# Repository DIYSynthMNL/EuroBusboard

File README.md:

# EuroBusboard

A Eurorack bus board with **8 module slots**, distributing **±12V + GND** across multiple connector formats. The project has three PCB variants in the same KiCad project: **10-pin IDC + JST combined**, **10-pin IDC only**, and **JST only**.

> For the Doepfer-standard 16-pin IDC variant (with `+5V`, `CV`, `Gate` rails additionally distributed), see the sibling repo: **[EuroBusboard-8-IDC-16PIN](https://github.com/DIYSynthMNL/EuroBusboard-8-IDC-16PIN)**.

## Variants

The KiCad project contains four configurations. Pick one when fabricating the PCB:

| Variant | KiCad file | Per-slot connectors | Use case |
|---|---|---|---|
| **16-pin IDC** (Doepfer A-100) | (in separate repo: [EuroBusboard-8-IDC-16PIN](https://github.com/DIYSynthMNL/EuroBusboard-8-IDC-16PIN)) | 1× 16-pin IDC | Modules with full Doepfer ribbon cables (±12V + GND + +5V + CV + Gate) |
| **10-pin IDC + JST (combined)** | `eurobusboard_idc_jst_8.kicad_pcb` | 1× 10-pin IDC + 1× 3-pin JST | Maximum flexibility — accepts both connector types per slot |
| **10-pin IDC only** | `eurobusboard_idc_8.kicad_pcb` | 1× 10-pin IDC | Compact, IDC-only modules |
| **JST only** | `eurobusboard_jst_8.kicad_pcb` | 1× 3-pin JST | DIY modules that use only the 3-pin JST power input |

All variants share the same power-input + reverse-protection + filter section. Only the per-slot connectors differ.

## Pinout (10-pin IDC, Eurorack subset of Doepfer A-100)

Looking at the IDC connector with the keyway (red stripe) on the *bottom*:

```
Pin   10  9   8   7   6   5   4   3   2   1
      +12 +12 GND GND GND GND GND GND -12 -12
```

`-12V` is on pin 1 / 2 (the red-stripe side) — Eurorack convention. `+12V` is on pin 9 / 10 (opposite side). Six GND pins in the middle provide low-impedance ground return.

The **3-pin JST** is:

| JST pin | Net |
|---|---|
| 1 | +12V |
| 2 | GND |
| 3 | -12V |

## Schematic

- Latest: **Rev 0.1** ([EuroBusboard-Schematic-rev0.1.pdf](Schematic%20PDFs/EuroBusboard-Schematic-rev0.1.pdf)) — 3 sheets, one per non-16-pin variant

## Power input / protection

Same circuit on all three sheets, just renamed nets per variant:

```
External ±12V supply
   │
   ├──[D3 / D14 / D9   1N4007 reverse-polarity diode on +12V]──┬── +12V bus
   │                                                            │
   │                                                            [C1 / C7 / C5   100µF bulk cap]
   │                                                            │
   │                                                            [D1 / D13 / D11  +12V indicator LED + R1/R7/R5 10K]
   │
   └──[D4 / D16 / D10  1N4007 reverse-polarity diode on -12V]──┬── -12V bus
                                                                │
                                                                [C2 / C8 / C6   100µF bulk cap]
                                                                │
                                                                [D2 / D15 / D12  -12V indicator LED + R2/R8/R6 10K]
```

Additional features (combined-variant only):
- **Power Thru** (J20, J21) — daisy-chain to another bus board
- **Test points** TP1 (+12V), TP2 (GND), TP3 (-12V) for DMM probing

## Design notes

**1N4007 diodes have a real voltage drop.** At a peak transient current of 1 A across each rail (with all 8 modules pulling momentarily), the diode drops about **1.0 V** — modules see only ~11 V on the rail instead of 12 V. For most analog modules this is harmless; for tight regulators (e.g. an LM7805 regulating to +5V from +12V supply that's actually 11V), it can reduce headroom. **A 1N5817 Schottky (~0.4 V drop)** would be a near-drop-in upgrade. See [issue](../../issues).

**No +5V or CV/Gate rails.** The 10-pin IDC variants don't distribute +5V (which most digital modules need) or CV/Gate (which the Doepfer A-100 standard provides for keyboard-bus signals). Modules requiring +5V must generate their own (via a 78M05 + the +12V rail — which is what most DIYSynthMNL modules do). For full Doepfer compatibility, use the 16-pin IDC variant in [EuroBusboard-8-IDC-16PIN](https://github.com/DIYSynthMNL/EuroBusboard-8-IDC-16PIN).

**Bulk capacitance.** 100 µF at the input is reasonable for a small case. For a fully-loaded board with current-hungry modules (digital sequencers, OLEDs, several VCAs), consider adding ~10 µF ceramics near each IDC connector for transient suppression.

## License

[GPLv3](LICENSE) — strong copyleft. **Note:** this is different from most DIYSynthMNL modules (which use CC-BY-NC-SA 4.0 for hardware, MIT for firmware). Confirm this license is intentional — for a passive bus board, MIT or CC-BY-SA may be more appropriate. See [issue](../../issues).

## Build status

What's ready for builders today, and what's still on the TODO list:

- [x] Schematic — Rev 0.1 ([EuroBusboard-Schematic-rev0.1.pdf](Schematic%20PDFs/EuroBusboard-Schematic-rev0.1.pdf))
- [ ] PCB layout — in progress — four variants in `kicad/`, no rev marker yet
- [ ] Gerber files for fabrication — none yet
- [ ] BOM — bus boards are simple; the schematic doubles as the BOM (LED color, diode replacement to Schottky if you take the recommendation above, etc.)
- [x] Photos of an assembled board — see [photos/](photos/)
- [x] License — [LICENSE](LICENSE) (GPLv3 — see note above)

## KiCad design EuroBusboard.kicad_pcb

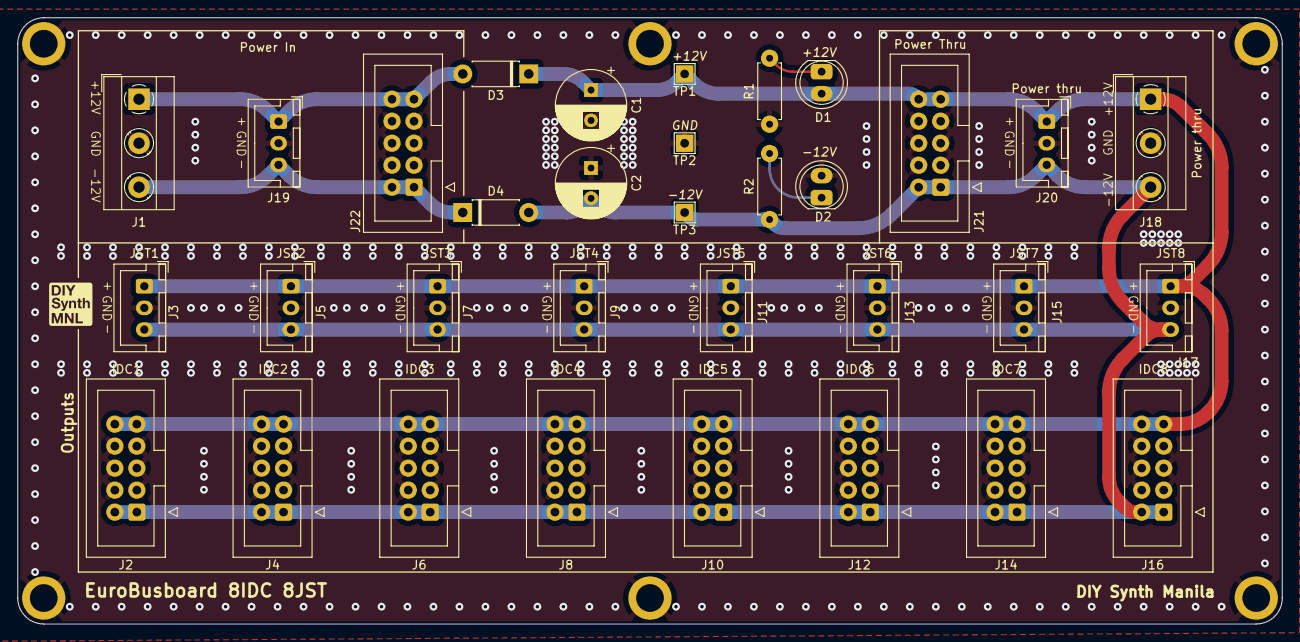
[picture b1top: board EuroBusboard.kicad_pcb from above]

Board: 2 copper layers, 146.0 x 70.0 mm, 39 parts (0 on the bottom side), 7 nets.

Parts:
C1, C2: 100uF; CP_Radial_D8.0mm_P3.50mm
D1: +12V; LED_D5.0mm_BigPads
D2: -12V; LED_D5.0mm_BigPads
D3, D4: 4007; D_DO-41_SOD81_P7.62mm_Horizontal_BigPads
H1, H2, H3, H4, H5, H6: MountingHole_Pad; MountingHole_M3_Standoff_Pad
J1: Power In; TerminalBlock_MetzConnect_Type101_RT01603HBWC_1x03_P5.08mm_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
J2: IDC1; IDC-Header_2x05_P2.54mm_Vertical_BigPads
J3: JST1; Eurorack_power_jst_3P
J4: IDC2; IDC-Header_2x05_P2.54mm_Vertical_BigPads
J5: JST2; Eurorack_power_jst_3P
J6: IDC3; IDC-Header_2x05_P2.54mm_Vertical_BigPads
J7: JST3; Eurorack_power_jst_3P
J8: IDC4; IDC-Header_2x05_P2.54mm_Vertical_BigPads
J9: JST4; Eurorack_power_jst_3P
J10: IDC5; IDC-Header_2x05_P2.54mm_Vertical_BigPads
J11: JST5; Eurorack_power_jst_3P
J12: IDC6; IDC-Header_2x05_P2.54mm_Vertical_BigPads
J13: JST6; Eurorack_power_jst_3P
J14: IDC7; IDC-Header_2x05_P2.54mm_Vertical_BigPads
J15: JST7; Eurorack_power_jst_3P
J16: IDC8; IDC-Header_2x05_P2.54mm_Vertical_BigPads
J17: JST8; Eurorack_power_jst_3P
J18: Power thru; TerminalBlock_MetzConnect_Type101_RT01603HBWC_1x03_P5.08mm_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
J19: Power In; Eurorack_power_jst_3P
J20: Power thru; Eurorack_power_jst_3P
J21: Power Thru; IDC-Header_2x05_P2.54mm_Vertical_BigPads
J22: Power In; IDC-Header_2x05_P2.54mm_Vertical_BigPads
R1, R2: 10K; R_quarter_watt_L6.3mm_D2.5mm_P7.62mm
TP1: +12V; TestPoint_THTPad_2.0x2.0mm_Drill1.0mm
TP2: GND; TestPoint_THTPad_2.0x2.0mm_Drill1.0mm
TP3: -12V; TestPoint_THTPad_2.0x2.0mm_Drill1.0mm

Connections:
/+12V: C1.1, D1.2 (A), D3.1 (K), J2.9 (+12V), J2.10 (+12V), J3.1 (+12v), J4.9 (+12V), J4.10 (+12V), J5.1 (+12v), J6.9 (+12V), J6.10 (+12V), J7.1 (+12v), J8.9 (+12V), J8.10 (+12V), J9.1 (+12v), J10.9 (+12V), J10.10 (+12V), J11.1 (+12v), J12.9 (+12V), J12.10 (+12V), J13.1 (+12v), J14.9 (+12V), J14.10 (+12V), J15.1 (+12v), J16.9 (+12V), J16.10 (+12V), J17.1 (+12v), J18.1, J20.1 (+12v), J21.9 (+12V), J21.10 (+12V), TP1.1
/+12V_IN: D3.2 (A), J1.1, J19.1 (+12v), J22.9 (+12V), J22.10 (+12V)
/-12V: C2.2, D4.2 (A), J2.1 (-12V), J2.2 (-12V), J3.3 (-12v), J4.1 (-12V), J4.2 (-12V), J5.3 (-12v), J6.1 (-12V), J6.2 (-12V), J7.3 (-12v), J8.1 (-12V), J8.2 (-12V), J9.3 (-12v), J10.1 (-12V), J10.2 (-12V), J11.3 (-12v), J12.1 (-12V), J12.2 (-12V), J13.3 (-12v), J14.1 (-12V), J14.2 (-12V), J15.3 (-12v), J16.1 (-12V), J16.2 (-12V), J17.3 (-12v), J18.3, J20.3 (-12v), J21.1 (-12V), J21.2 (-12V), R2.1, TP3.1
/-12V_IN: D4.1 (K), J1.3, J19.3 (-12v), J22.1 (-12V), J22.2 (-12V)
/GND: C1.2, C2.1, D2.2 (A), H1.1, H2.1, H3.1, H4.1, H5.1, H6.1, J1.2, J2.3 (GND), J2.4 (GND), J2.5 (GND), J2.6 (GND), J2.7 (GND), J2.8 (GND), J3.2 (GND), J4.3 (GND), J4.4 (GND), J4.5 (GND), J4.6 (GND), J4.7 (GND), J4.8 (GND), J5.2 (GND), J6.3 (GND), J6.4 (GND), J6.5 (GND), J6.6 (GND), J6.7 (GND), J6.8 (GND), J7.2 (GND), J8.3 (GND), J8.4 (GND), J8.5 (GND), J8.6 (GND), J8.7 (GND), J8.8 (GND), J9.2 (GND), J10.3 (GND), J10.4 (GND), J10.5 (GND), J10.6 (GND), J10.7 (GND), J10.8 (GND), J11.2 (GND), J12.3 (GND), J12.4 (GND), J12.5 (GND), J12.6 (GND), J12.7 (GND), J12.8 (GND), J13.2 (GND), J14.3 (GND), J14.4 (GND), J14.5 (GND), J14.6 (GND), J14.7 (GND), J14.8 (GND), J15.2 (GND), J16.3 (GND), J16.4 (GND), J16.5 (GND), J16.6 (GND), J16.7 (GND), J16.8 (GND), J17.2 (GND), J18.2, J19.2 (GND), J20.2 (GND), J21.3 (GND), J21.4 (GND), J21.5 (GND), J21.6 (GND), J21.7 (GND), J21.8 (GND), J22.3 (GND), J22.4 (GND), J22.5 (GND), J22.6 (GND), J22.7 (GND), J22.8 (GND), R1.1, TP2.1
unnamed: D1.1 (K), R1.2
unnamed: D2.1 (K), R2.2

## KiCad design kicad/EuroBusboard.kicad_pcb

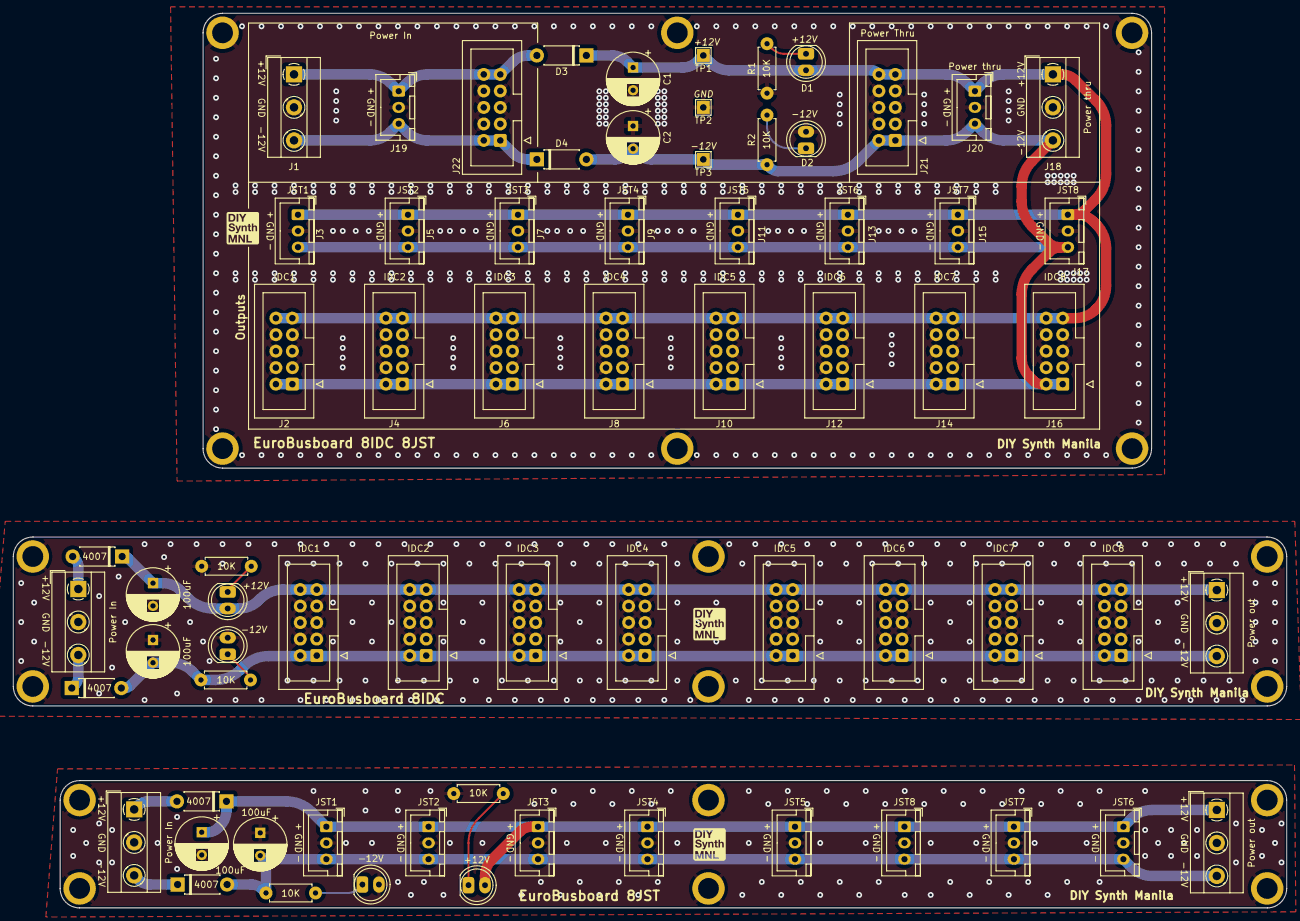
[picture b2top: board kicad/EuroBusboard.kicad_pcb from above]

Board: 2 copper layers, 196.0 x 137.7 mm, 90 parts (0 on the bottom side), 21 nets.

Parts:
B1, B2, B3: Board
C1, C2, C5, C6, C7, C8: 100uF; CP_Radial_D8.0mm_P3.50mm
D1, D11, D13: +12V; LED_D5.0mm_BigPads
D2, D12, D15: -12V; LED_D5.0mm_BigPads
D3, D4, D9, D10, D14, D16: 4007; D_DO-41_SOD81_P7.62mm_Horizontal_BigPads
H1, H2, H3, H4, H5, H6, H7, H8, H9, H10, H11, H12, H13, H14, H15, H16, H17, H18: MountingHole_Pad; MountingHole_M3_Standoff_Pad
J1, J41, J43: Power In; TerminalBlock_MetzConnect_Type101_RT01603HBWC_1x03_P5.08mm_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
J2, J23: IDC1; IDC-Header_2x05_P2.54mm_Vertical_BigPads
J3, J33: JST1; Eurorack_power_jst_3P
J4, J24: IDC2; IDC-Header_2x05_P2.54mm_Vertical_BigPads
J5, J34: JST2; Eurorack_power_jst_3P
J6, J25: IDC3; IDC-Header_2x05_P2.54mm_Vertical_BigPads
J7, J35: JST3; Eurorack_power_jst_3P
J8, J26: IDC4; IDC-Header_2x05_P2.54mm_Vertical_BigPads
J9, J36: JST4; Eurorack_power_jst_3P
J10, J27: IDC5; IDC-Header_2x05_P2.54mm_Vertical_BigPads
J11, J37: JST5; Eurorack_power_jst_3P
J12, J28: IDC6; IDC-Header_2x05_P2.54mm_Vertical_BigPads
J13, J38: JST6; Eurorack_power_jst_3P
J14, J29: IDC7; IDC-Header_2x05_P2.54mm_Vertical_BigPads
J15, J39: JST7; Eurorack_power_jst_3P
J16, J30: IDC8; IDC-Header_2x05_P2.54mm_Vertical_BigPads
J17, J40: JST8; Eurorack_power_jst_3P
J18: Power thru; TerminalBlock_MetzConnect_Type101_RT01603HBWC_1x03_P5.08mm_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
J19: Power In; Eurorack_power_jst_3P
J20: Power thru; Eurorack_power_jst_3P
J21: Power Thru; IDC-Header_2x05_P2.54mm_Vertical_BigPads
J22: Power In; IDC-Header_2x05_P2.54mm_Vertical_BigPads
J42, J44: Power out; TerminalBlock_MetzConnect_Type101_RT01603HBWC_1x03_P5.08mm_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
R1, R2, R5, R6, R7, R8: 10K; R_quarter_watt_L6.3mm_D2.5mm_P7.62mm
TP1: +12V; TestPoint_THTPad_2.0x2.0mm_Drill1.0mm
TP2: GND; TestPoint_THTPad_2.0x2.0mm_Drill1.0mm
TP3: -12V; TestPoint_THTPad_2.0x2.0mm_Drill1.0mm

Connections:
/+12V: C1.1, D1.2 (A), D3.1 (K), J2.9 (+12V), J2.10 (+12V), J3.1 (+12v), J4.9 (+12V), J4.10 (+12V), J5.1 (+12v), J6.9 (+12V), J6.10 (+12V), J7.1 (+12v), J8.9 (+12V), J8.10 (+12V), J9.1 (+12v), J10.9 (+12V), J10.10 (+12V), J11.1 (+12v), J12.9 (+12V), J12.10 (+12V), J13.1 (+12v), J14.9 (+12V), J14.10 (+12V), J15.1 (+12v), J16.9 (+12V), J16.10 (+12V), J17.1 (+12v), J18.1, J20.1 (+12v), J21.9 (+12V), J21.10 (+12V), TP1.1
/+12V_IN: D3.2 (A), J1.1, J19.1 (+12v), J22.9 (+12V), J22.10 (+12V)
/-12V: C2.2, D4.2 (A), J2.1 (-12V), J2.2 (-12V), J3.3 (-12v), J4.1 (-12V), J4.2 (-12V), J5.3 (-12v), J6.1 (-12V), J6.2 (-12V), J7.3 (-12v), J8.1 (-12V), J8.2 (-12V), J9.3 (-12v), J10.1 (-12V), J10.2 (-12V), J11.3 (-12v), J12.1 (-12V), J12.2 (-12V), J13.3 (-12v), J14.1 (-12V), J14.2 (-12V), J15.3 (-12v), J16.1 (-12V), J16.2 (-12V), J17.3 (-12v), J18.3, J20.3 (-12v), J21.1 (-12V), J21.2 (-12V), R2.1, TP3.1
/-12V_IN: D4.1 (K), J1.3, J19.3 (-12v), J22.1 (-12V), J22.2 (-12V)
/EuroBusboard8_IDC/+12VIN_IDC: D14.2 (A), J43.1
/EuroBusboard8_IDC/+12V_IDC: C7.1, D13.2 (A), D14.1 (K), J23.9 (+12V), J23.10 (+12V), J24.9 (+12V), J24.10 (+12V), J25.9 (+12V), J25.10 (+12V), J26.9 (+12V), J26.10 (+12V), J27.9 (+12V), J27.10 (+12V), J28.9 (+12V), J28.10 (+12V), J29.9 (+12V), J29.10 (+12V), J30.9 (+12V), J30.10 (+12V), J44.1
/EuroBusboard8_IDC/-12VIN_IDC: D16.1 (K), J43.3
/EuroBusboard8_IDC/-12V_IDC: C8.2, D16.2 (A), J23.1 (-12V), J23.2 (-12V), J24.1 (-12V), J24.2 (-12V), J25.1 (-12V), J25.2 (-12V), J26.1 (-12V), J26.2 (-12V), J27.1 (-12V), J27.2 (-12V), J28.1 (-12V), J28.2 (-12V), J29.1 (-12V), J29.2 (-12V), J30.1 (-12V), J30.2 (-12V), J44.3, R8.1
/EuroBusboard8_IDC/GND_IDC: C7.2, C8.1, D15.2 (A), H7.1, H8.1, H9.1, H10.1, H11.1, H12.1, J23.3 (GND), J23.4 (GND), J23.5 (GND), J23.6 (GND), J23.7 (GND), J23.8 (GND), J24.3 (GND), J24.4 (GND), J24.5 (GND), J24.6 (GND), J24.7 (GND), J24.8 (GND), J25.3 (GND), J25.4 (GND), J25.5 (GND), J25.6 (GND), J25.7 (GND), J25.8 (GND), J26.3 (GND), J26.4 (GND), J26.5 (GND), J26.6 (GND), J26.7 (GND), J26.8 (GND), J27.3 (GND), J27.4 (GND), J27.5 (GND), J27.6 (GND), J27.7 (GND), J27.8 (GND), J28.3 (GND), J28.4 (GND), J28.5 (GND), J28.6 (GND), J28.7 (GND), J28.8 (GND), J29.3 (GND), J29.4 (GND), J29.5 (GND), J29.6 (GND), J29.7 (GND), J29.8 (GND), J30.3 (GND), J30.4 (GND), J30.5 (GND), J30.6 (GND), J30.7 (GND), J30.8 (GND), J43.2, J44.2, R7.1
/EuroBusboard8_JST/+12VIN_JST: D9.2 (A), J41.1
/EuroBusboard8_JST/+12V_JST: C5.1, D9.1 (K), D11.2 (A), J33.1 (+12v), J34.1 (+12v), J35.1 (+12v), J36.1 (+12v), J37.1 (+12v), J38.1 (+12v), J39.1 (+12v), J40.1 (+12v), J42.1
/EuroBusboard8_JST/-12VIN_JST: D10.1 (K), J41.3
/EuroBusboard8_JST/-12V_JST: C6.2, D10.2 (A), J33.3 (-12v), J34.3 (-12v), J35.3 (-12v), J36.3 (-12v), J37.3 (-12v), J38.3 (-12v), J39.3 (-12v), J40.3 (-12v), J42.3, R6.1
/EuroBusboard8_JST/GND_JST: C5.2, C6.1, D12.2 (A), H13.1, H14.1, H15.1, H16.1, H17.1, H18.1, J33.2 (GND), J34.2 (GND), J35.2 (GND), J36.2 (GND), J37.2 (GND), J38.2 (GND), J39.2 (GND), J40.2 (GND), J41.2, J42.2, R5.1
/GND: C1.2, C2.1, D2.2 (A), H1.1, H2.1, H3.1, H4.1, H5.1, H6.1, J1.2, J2.3 (GND), J2.4 (GND), J2.5 (GND), J2.6 (GND), J2.7 (GND), J2.8 (GND), J3.2 (GND), J4.3 (GND), J4.4 (GND), J4.5 (GND), J4.6 (GND), J4.7 (GND), J4.8 (GND), J5.2 (GND), J6.3 (GND), J6.4 (GND), J6.5 (GND), J6.6 (GND), J6.7 (GND), J6.8 (GND), J7.2 (GND), J8.3 (GND), J8.4 (GND), J8.5 (GND), J8.6 (GND), J8.7 (GND), J8.8 (GND), J9.2 (GND), J10.3 (GND), J10.4 (GND), J10.5 (GND), J10.6 (GND), J10.7 (GND), J10.8 (GND), J11.2 (GND), J12.3 (GND), J12.4 (GND), J12.5 (GND), J12.6 (GND), J12.7 (GND), J12.8 (GND), J13.2 (GND), J14.3 (GND), J14.4 (GND), J14.5 (GND), J14.6 (GND), J14.7 (GND), J14.8 (GND), J15.2 (GND), J16.3 (GND), J16.4 (GND), J16.5 (GND), J16.6 (GND), J16.7 (GND), J16.8 (GND), J17.2 (GND), J18.2, J19.2 (GND), J20.2 (GND), J21.3 (GND), J21.4 (GND), J21.5 (GND), J21.6 (GND), J21.7 (GND), J21.8 (GND), J22.3 (GND), J22.4 (GND), J22.5 (GND), J22.6 (GND), J22.7 (GND), J22.8 (GND), R1.1, TP2.1
unnamed: D1.1 (K), R1.2
unnamed: D2.1 (K), R2.2
unnamed: D11.1 (K), R5.2
unnamed: D12.1 (K), R6.2
unnamed: D13.1 (K), R7.2
unnamed: D15.1 (K), R8.2

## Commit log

2024-01-01 Schematic rev0.1 update
2024-01-02 PCB finished
2024-01-02 board update
2024-01-02 added idc and jst only bus boards
2024-01-02 separated boards using kikit
2024-01-10 schematic pdf update
2024-01-22 added kicad gitignore
2024-01-27 cleaned up project directory
2026-05-14 Improve README and clean up repo
2026-05-14 Add Build status checklist to README
2026-05-14 Fix Build status link path case
2026-05-14 Rewrite Build status with per-module accuracy
2026-05-14 Add photos/ placeholder for assembled-module shots
2026-05-14 Add JPGs converted from raws and clean photo dirs
2026-05-14 Rename photos to descriptive names; pick hero images
2026-05-15 Deep-dive rewrite: README with variant matrix, pinout, design notes
    Restructures the README to clearly explain the 4 variants (16-pin IDC
    sibling, 10-pin IDC+JST combined, 10-pin IDC-only, JST-only), the
    Doepfer-subset pinout, and design notes about 1N4007 voltage drop
    and the absence of +5V/CV/Gate rails on the 10-pin variants.
    Flags the GPLv3 license as unusual for hardware (most open-hardware
    projects use CERN-OHL or CC-BY-SA) and recommends review.
